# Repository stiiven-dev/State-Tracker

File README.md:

<h1 align="center">🧓 State Tracker</h1>

<p align="center">
Wearable monitoring system for elderly safety and health tracking
</p>

---

# 📖 Definition

**State Tracker** is a wearable monitoring device designed to help elderly people who live alone.  
The system continuously monitors biometric and motion data to detect dangerous situations such as falls or abnormal physiological states.

If a risk is detected, the system automatically alerts caregivers or guardians through a communication system.

---

# 🎯 Project Objective

The goal of this project is to:

- Monitor elderly health conditions
- Detect dangerous situations such as falls
- Provide real-time alerts
- Allow caregivers to track the user's state remotely

This system aims to increase the safety and independence of elderly individuals living alone.

---

# ⚠️ Disclaimer

This device is designed for elderly people living alone.

It is **NOT intended for patients with**:

- Dementia
- Alzheimer’s disease
- Urinary disorders

These conditions require continuous medical supervision.

---

# 🧠 System Overview

The system collects **biometric and motion data** using sensors embedded in a wearable device.

The data is processed by a microcontroller and analyzed to detect abnormal situations.

If a dangerous state is detected, the system triggers an alert that is sent to caregivers via communication modules.

---

# 🏗 System Architecture

## Global System Architecture

### Explanation

1. **Power System**

The Power System provides the electrical energy required for the entire device.

It includes:

- Battery supply
- Power management circuitry

This subsystem ensures that all hardware components operate reliably and efficiently while maintaining low power consumption for wearable usage.

---

2. **Sensors Subsystem**

The Sensors Subsystem is responsible for collecting real-time physical and physiological data from the user.

The system integrates several sensors:

- Accelerometer → detects movement and sudden impacts
- Gyroscope → measures orientation and body rotation
- Physiological Sensors → monitor biometric signals such as heart rate and oxygen levels

These sensors provide the raw data required to monitor the user’s state.

---

3. **Embedded Processing Unit**

The Embedded Processing Unit acts as the core controller of the system.

Its main responsibilities include:

- Data acquisition from sensors
- Signal processing to interpret sensor data
- Feature extraction to identify relevant patterns

This processing stage prepares the data for the detection algorithms.

---

4. **Detection & Decision Unit**

This module analyzes the processed data to determine whether the user is in a safe or dangerous condition.

The system performs:

- Fall detection logic
- Abnormal behaviour analysis
- Threshold comparison

Based on these analyses, the system determines whether the user is in a normal state or a dangerous situation.

---

5. **Normal State Monitoring**

If the system detects normal activity, monitoring continues without any alert.

The sensors keep collecting data and the processing unit continues analyzing the user’s movements and physiological signals.

---

6. **Dangerous Event Detection**

When the system confirms a dangerous event such as:

- A fall
- Abnormal physiological values
- Unusual behaviour patterns

the alert mechanism is activated.

---

7. **Communication Module**

The Communication Module transmits alerts and data to external systems.

Supported communication technologies include:

- Bluetooth
- GSM
- WiFi

These technologies allow the system to send notifications even if the user is alone.

---

8. **Mobile Application**

The Mobile Application serves as the user interface for caregivers.

It provides features such as:

- Alert visualization
- User monitoring dashboard
- Event history tracking
- Cloud synchronization

This application allows caregivers to monitor the elderly user remotely.

---

9. **Mobile Application**

When a dangerous event is detected, the system immediately sends a notification to caregivers.
Alerts may be delivered via:

- Push notifications
- SMS messages

This ensures a rapid response to emergencies and improves the safety of elderly individuals living alone.

---

# 🔄 Data Flow

### Explanation

1. The elderly user wears the monitoring device.

2. Sensors collect raw data including:

- Movement
- Acceleration
- Physiological signals

3. Data preprocessing removes noise and filters signals.

4. The danger detection algorithm analyzes the cleaned data.

5. If the system detects normal activity, monitoring continues.

6. If a dangerous state is detected:

- An alert is generated
- A message is sent to caregivers

---

# 🔧 Hardware Components

| Component          | Purpose                                         |
| ------------------ | ----------------------------------------------- |
| **ESP32 S3**       | Main microcontroller with wireless capabilities |
| **MAX30102**       | Heart rate and blood oxygen monitoring          |
| **MPU6050**        | Motion tracking and fall detection              |
| **GSM Module**     | Sending emergency messages                      |
| **TVS Protection** | Static discharge protection                     |

---

# 💻 Technologies Used

- **JavaScript**
- Embedded systems
- IoT sensors
- Mobile communication
- Signal processing

---

Clone the repository:

```bash
git clone https://github.com/stiiven-dev/State-Tracker.git
cd State-Tracker
```

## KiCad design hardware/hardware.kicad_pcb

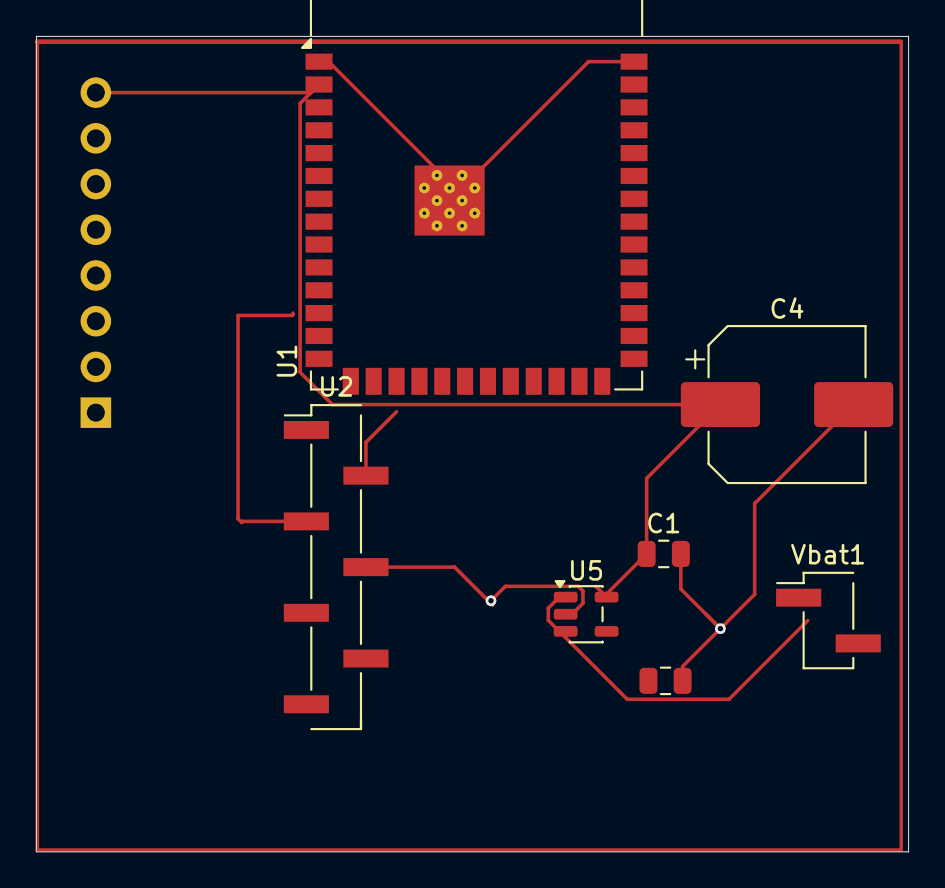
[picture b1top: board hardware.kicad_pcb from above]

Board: 2 copper layers, 48.4 x 45.3 mm, 8 parts (1 on the bottom side), 5 nets.

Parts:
C1, C2: C; C_0805_2012Metric
C4: C_Polarized; CP_Elec_8x10.5
U1: ESP32-S3-WROOM-1
U2: MAX30102; PinHeader_1x07_P2.54mm_Vertical_SMD_Pin1Left
U3: MPU-6050; PinHeader_1x08_P2.54mm_Vertical
U5: XC6204B332MR-SOT23-5; SOT-23-5
Vbat1: Conn_01x02_Pin; PinHeader_1x02_P2.54mm_Vertical_SMD_Pin1Left

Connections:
+3V3: C1.1, C4.1, U1.2 (3V3), U1.3 (EN), U3.8 (VLOGIC_8), U5.5 (VOUT)
GND: C1.2, C2.2, C4.2, U1.1 (GND), U1.40 (GND), U1.41 (GND), U2.4 (PGND), U5.2 (VSS)
unnamed: U1.12 (IO8), U2.3 (SDA)
unnamed: U1.17 (IO9), U2.2 (SCL)
unnamed: C2.1, U5.1 (VIN), U5.3 (CE)

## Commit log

2026-03-05 adding gitignore file/completing folders
2026-03-05 Add project folder struct
2026-03-06 README.md
2026-03-09 fixing doc files
2026-03-19 docs: corrected esp in use
2026-03-25 add: connectToMobile if no ssid/pwd stored
2026-03-25 heart sensor code test
2026-03-25 adding lib files
2026-03-25 fix: update include paths for heart sensor libraries
2026-03-25 refactor: update heart_update and heart_handle_logic functions for improved data handling
2026-03-26 add: uploading data to supabase
2026-03-26 docs: explained how connectToMobile works
2026-03-26 docs: commented the code to explain it
2026-03-26 docs: readme explaning workflow of sendToCloud
2026-03-28 add store files
2026-03-28 Update README.md to reflect store.cpp removal
    Removed reference to the non-existent store.cpp file and updated the storeData function signature section.
2026-04-05 Initial commit: Add schematic for ESP32-S3 and power supply stages
2026-04-10 add alert
2026-04-11 upgrading circuits and power supplies circuit
2026-04-11 Add hardware directory with KiCad PCB files
2026-04-11 fix: upload to database every 90s
2026-04-12 delete: remove hardware subproject directory
